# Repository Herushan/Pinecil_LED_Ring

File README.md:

# Pinecil_LED_Ring
Finished board with ideal LED combination.

White boards are shown are with smaller holes and new design (November 2023) has larger holes with better spacing and have the two LED methods of assembly shown (can use SMD on the through hole pads as shown). The yellow board is 1st draft of 3 LED design that missed some PCB info.
 New updated wire connection holes that are oval and square (November 2023). 

LED ring attachment for the Pinecil V2 soldering iron (should work for V1 as well as it goes on the body)
Recommend looking at the pictures and details to the inital two LED writeup (Pinecil_LED_Ring_writeup.pdf) that is here in the GitHub. The square holes are negative and round is positive. Arrow points to negative or left looking at board with LED at bottom.

The board is all done in KiCad and the zip file is all you need to produce a board. 
The LED is a 3mm LED with a third LED that is 0805
The SMD resistor is an 0805 with hand soldering footprint
Updated with an 0805 LED on the bottom to help with shadowing.

Kit with all the parts.

Assembly of kit video (Video of soldering to Pinecil V2 coming later)
https://youtu.be/LMbjwjDbSew
Assembly to Pinecil
https://youtu.be/VbyIGmIXqKs

Calculate your resistor based on the LED you choose and the power source form the Pinecil you decide to use as well. Resistor should be around 75ohms with 3.2V forward voltage and 20 mA forward current on the LED.

Recommend soldering (being careful small gap and size to board holes) the power and ground with sold strand wire preferrably to the holes and to the iron. Wire should be small as 30/32 awg is currently what I am using but hole supports upto .015 inch wire which should be around 26 awg max.

***May not happen*** Will update to SPI controlled lights when a known SPI connection is possible. This might not come and optional mod to add switch for on/off control for those that do not want to always be on will be looked at. I actually find it always being on nice.

Recommend reading the wiki (https://wiki.pine64.org/wiki/Pinecil) for guides to opening the Pinecil (https://www.youtube.com/watch?v=aK01V5DrrVk).

The info on size of board according to Oshpark is: 2 layer board of 0.84 x 0.67 inches (21.2 x 17.1 mm)
Any 3mm through hole LED will work.
SMD LED that works for the pad: https://www.digikey.com/en/products/detail/harvatek-corporation/B1701TX-20P000614U1930/16671745
Resistor that works: https://www.digikey.com/en/products/detail/rohm-semiconductor/ESR10EZPF75R0/1983560

Contact me on discord (@ahall(RuShan)) on the Pine64 channel for any questions through DM is fine.
If you would like to use my referral link to elecrow for boards: https://www.elecrow.com/referral-program/MTM5NjdqMnQ/

I also shared the project on Elecrow here: https://www.elecrow.com/sharepj/pinecil-led-ring-add-on-358.html

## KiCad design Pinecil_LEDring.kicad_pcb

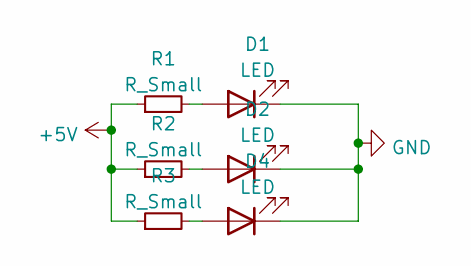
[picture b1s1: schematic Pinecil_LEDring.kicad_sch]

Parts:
D1, D2: LED; LED-3MM
D4: LED; LED_0805_2012Metric_Pad1.15x1.40mm_HandSolder
R1, R2, R3: R_Small; R_0603_HandSoldering

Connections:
+5V: R1.1, R2.1, R3.1
GND: D1.1 (K), D2.1 (K), D4.1 (K)
unnamed: D1.2 (A), R1.2
unnamed: D2.2 (A), R2.2
unnamed: D4.2 (A), R3.2

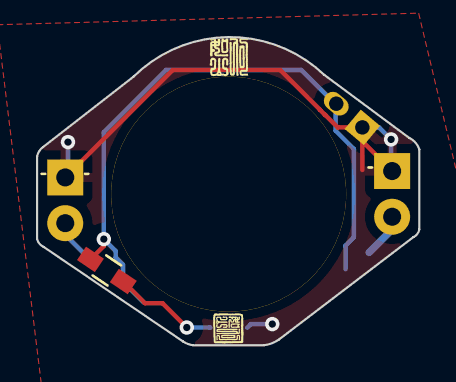
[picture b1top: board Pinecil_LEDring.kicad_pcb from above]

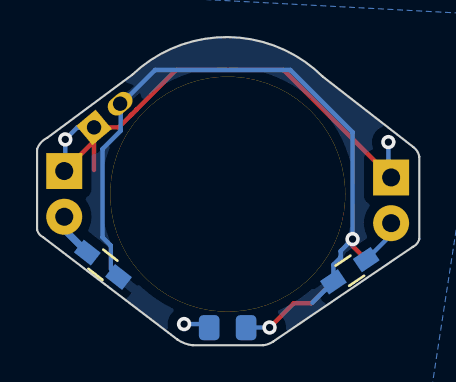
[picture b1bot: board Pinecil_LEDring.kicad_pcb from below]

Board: 2 copper layers, 21.2 x 17.1 mm, 7 parts (3 on the bottom side), 5 nets.

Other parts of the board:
Pinecil LED Ring: Pinecil_LEDring

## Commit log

2022-12-21 Add files via upload
    Original 2 LED ring write up.
2023-04-03 Delete Pinecil_LEDring_Back_nontip.png
    Old 2 LED image
2023-04-03 Delete Pinecil_LEDring_Front_nontip.png
    Old 2 LED image
2023-04-03 Update README.md
    Added pictures to the readme per an issue that was given and updated some wording.
2023-04-03 Update README.md
    Fixed minor information issues.
2023-11-19 Added updated design files and gerbers
    Updated the design off the board to make soldering the wires easier.
